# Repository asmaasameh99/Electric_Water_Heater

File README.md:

# Electric_Water_Heater
Design of electric water heater using PIC microcontroller

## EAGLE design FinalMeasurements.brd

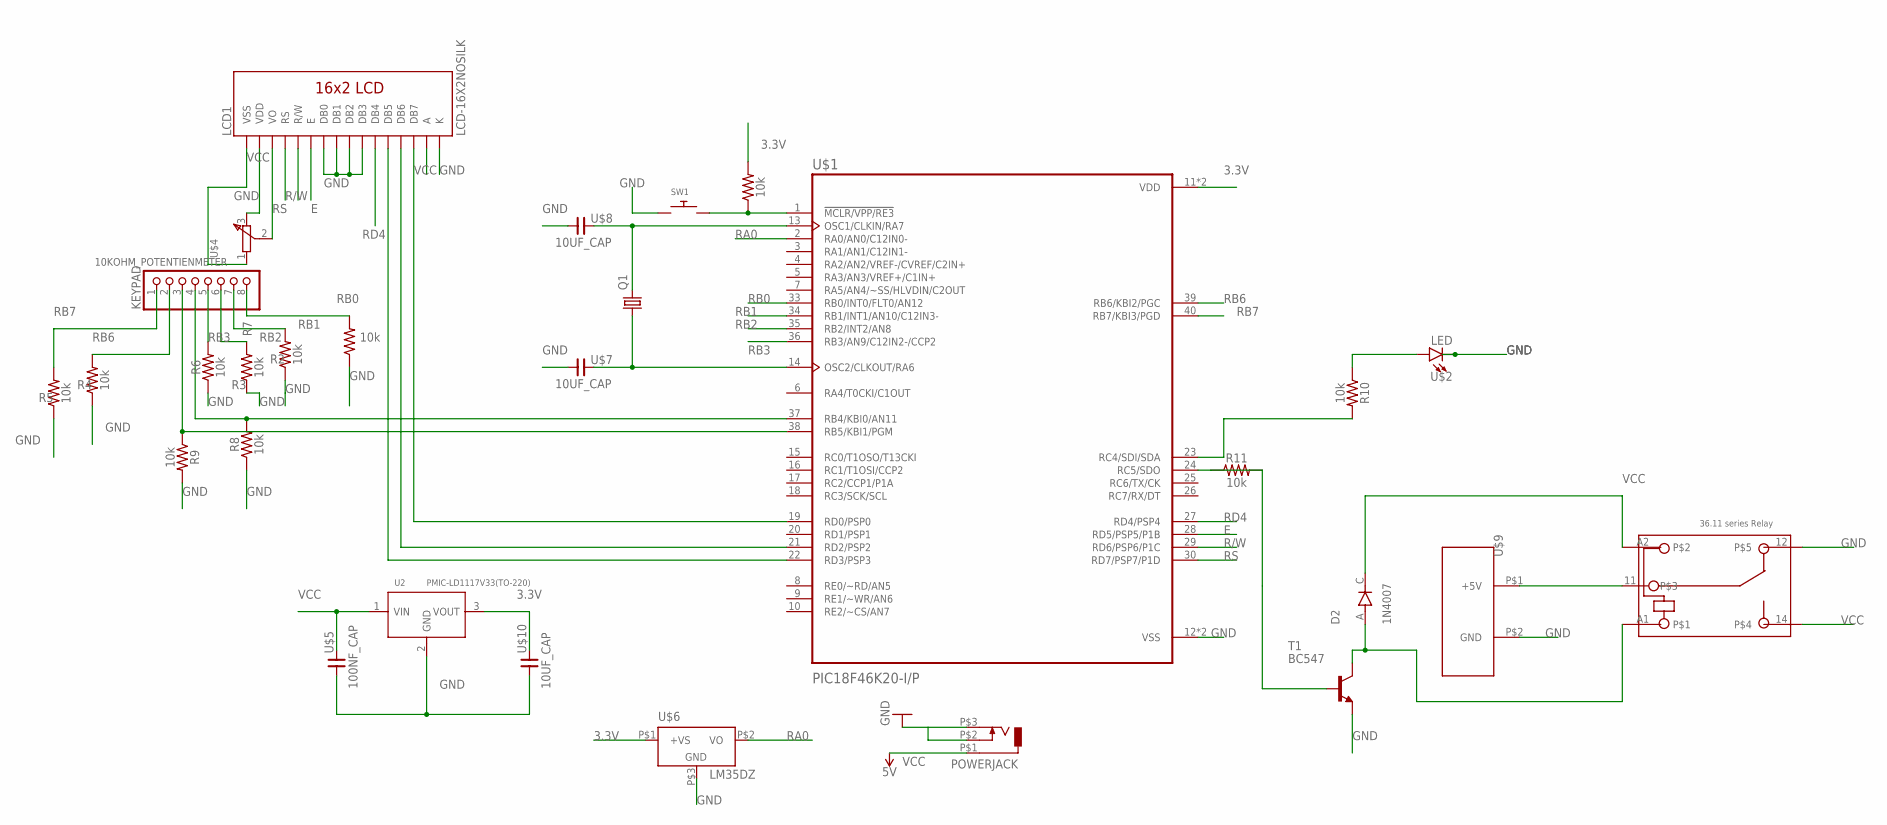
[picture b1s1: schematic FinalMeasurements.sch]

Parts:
D2: 1N4007; DIOAD1060W80L520D270
K1: 5V_RELAY; RELAY_FOOTPRINT
KEYPAD: KEYPAD_4X4MATRIXBIG; 1X08-BIG
LCD1: LCD-16X2NOSILK; LCD-16X2_NOSILK
POWERJACK: DCJ0303
Q1: CRYSTALHC49U-V; HC49U-V
R1, R2, R3, R4, R5, R6, R7, R8, R9, R10, R11: 10k; AXIAL-0.3
SW1: SWITCH_PUSHBUTTONEVQ-PE; TACT_PANA-EVQ
T1: BC547; TO92
U2: PMIC-LD1117V33(TO-220); TO-220
U$1: PIC18F46K20-I/P; DIP1540W47P254L5320H635Q40B
U$2: LED; LED_3MM
U$4: 10KOHM_POTENTIENMETER; POTENTIOMETER_FOOTPRINT
U$5: 100NF_CAP; C025-040X018
U$6: LM35DZ; LM35DZ_FOOTPRINT
U$7, U$8, U$10: 10UF_CAP; C025-040X018
U$9: DC_FAN; DC_FAN_FOOTPRINT

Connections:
3.3V: R1.P$2 (2), U2.3 (VOUT), U$1.11 (VDD), U$1.32 (VDD), U$6.P$1 (+VS), U$10.2
E: LCD1.6 (E), U$1.28 (RD5/PSP5/P1B)
GND: K1.12, LCD1.1 (VSS), LCD1.7 (DB0), LCD1.8 (DB1), LCD1.9 (DB2), LCD1.10 (DB3), LCD1.16 (K), POWERJACK.P$2 (2), POWERJACK.P$3 (3), R2.P$1 (1), R3.P$1 (1), R4.P$1 (1), R5.P$1 (1), R6.P$1 (1), R7.P$1 (1), R8.P$1 (1), R9.P$2 (2), SW1.P$1, T1.1 (E), U2.2 (GND), U$1.12 (VSS), U$1.31 (VSS), U$2.K (C), U$4.1, U$5.1, U$6.P$3 (GND), U$7.1, U$8.1, U$9.P$2 (GND), U$10.1
unnamed: R1.P$1 (1), SW1.P$2, U$1.1 (!MCLR/VPP/RE3)
unnamed: Q1.2, U$1.13 (OSC1/CLKIN/RA7), U$8.2
unnamed: Q1.1, U$1.14 (OSC2/CLKOUT/RA6), U$7.2
unnamed: R10.P$1 (1), U$2.A
unnamed: LCD1.12 (DB5), U$1.22 (RD3/PSP3)
unnamed: LCD1.13 (DB6), U$1.21 (RD2/PSP2)
unnamed: LCD1.14 (DB7), U$1.19 (RD0/PSP0)
unnamed: KEYPAD.3, R9.P$1 (1), U$1.38 (RB5/KBI1/PGM)
unnamed: R10.P$2 (2), U$1.23 (RC4/SDI/SDA)
unnamed: LCD1.3 (VO), U$4.2
unnamed: KEYPAD.4, R8.P$2 (2), U$1.37 (RB4/KBI0/AN11)
unnamed: D2.A, K1.A1, T1.3 (C)
unnamed: R11.P$1 (1), U$1.24 (RC5/SDO)
unnamed: K1.11, U$9.P$1 (+5V)
unnamed: R11.P$2 (2), T1.2 (B)
R/W: LCD1.5 (R/W), U$1.29 (RD6/PSP6/P1C)
RA0: U$1.2 (RA0/AN0/C12IN0-), U$6.P$2 (VO)
RB0: KEYPAD.8, R7.P$2 (2), U$1.33 (RB0/INT0/FLT0/AN12)
RB1: KEYPAD.7, R2.P$2 (2), U$1.34 (RB1/INT1/AN10/C12IN3-)
RB2: KEYPAD.6, R3.P$2 (2), U$1.35 (RB2/INT2/AN8)
RB3: KEYPAD.5, R6.P$2 (2), U$1.36 (RB3/AN9/C12IN2-/CCP2)
RB6: KEYPAD.2, R4.P$2 (2), U$1.39 (RB6/KBI2/PGC)
RB7: KEYPAD.1, R5.P$2 (2), U$1.40 (RB7/KBI3/PGD)
RD4: LCD1.11 (DB4), U$1.27 (RD4/PSP4)
RS: LCD1.4 (RS), U$1.30 (RD7/PSP7/P1D)
VCC: D2.C, K1.14, K1.A2, LCD1.2 (VDD), LCD1.15 (A), POWERJACK.P$1 (1), U2.1 (VIN), U$4.3, U$5.2

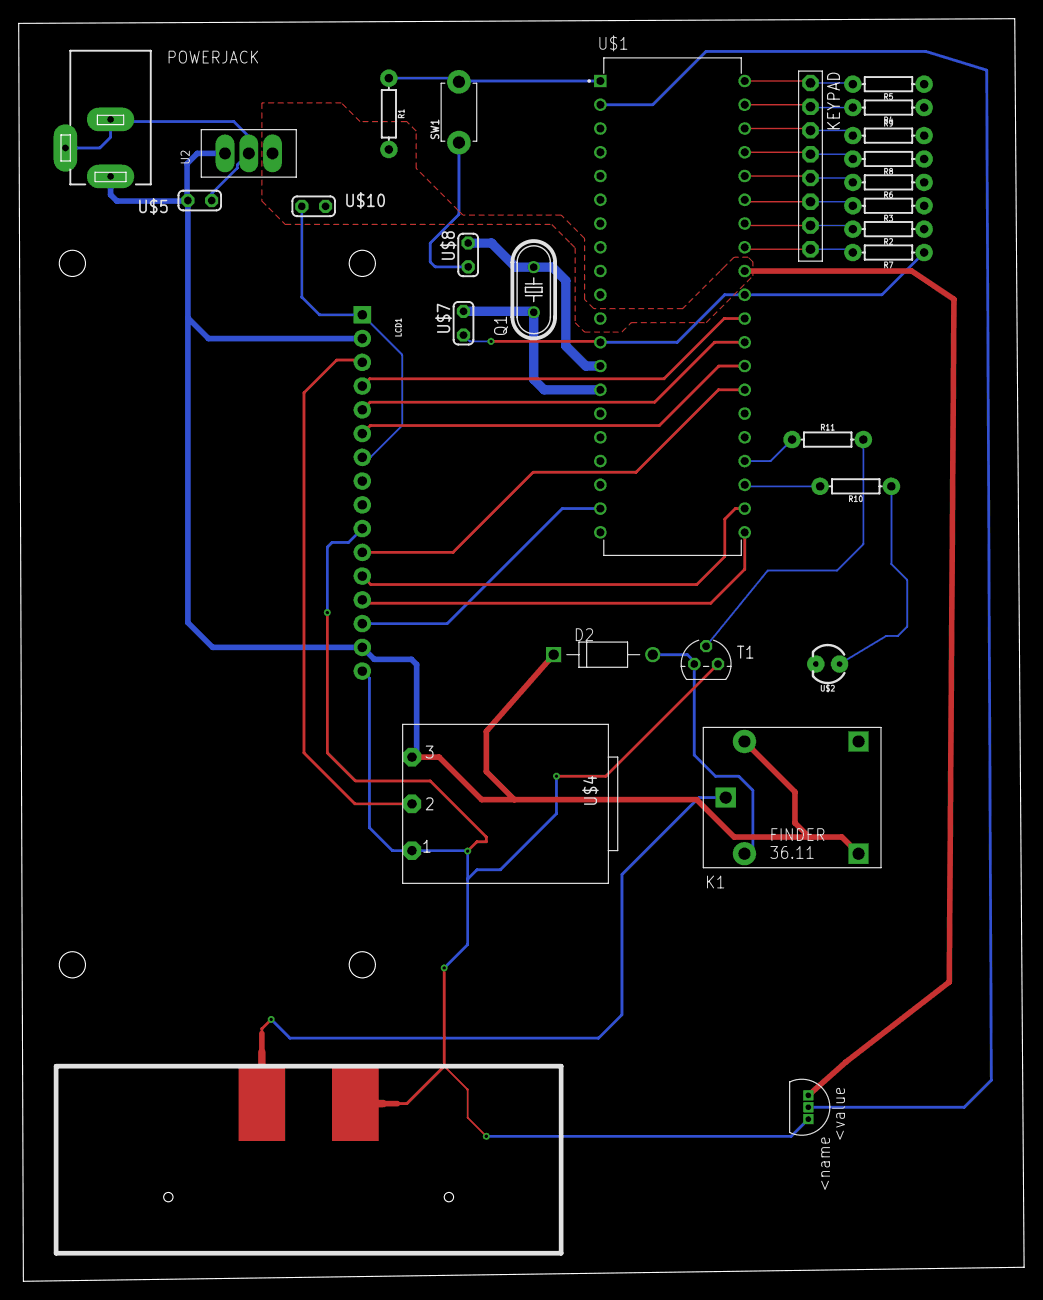
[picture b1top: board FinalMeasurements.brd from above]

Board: 2 copper layers, 107.5 x 135.0 mm, 29 parts (0 on the bottom side), 29 nets.
